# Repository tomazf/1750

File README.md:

# 1750
remote BH1750 light sensor node

HW currently supporting 5 sensors connected over SoftWire library

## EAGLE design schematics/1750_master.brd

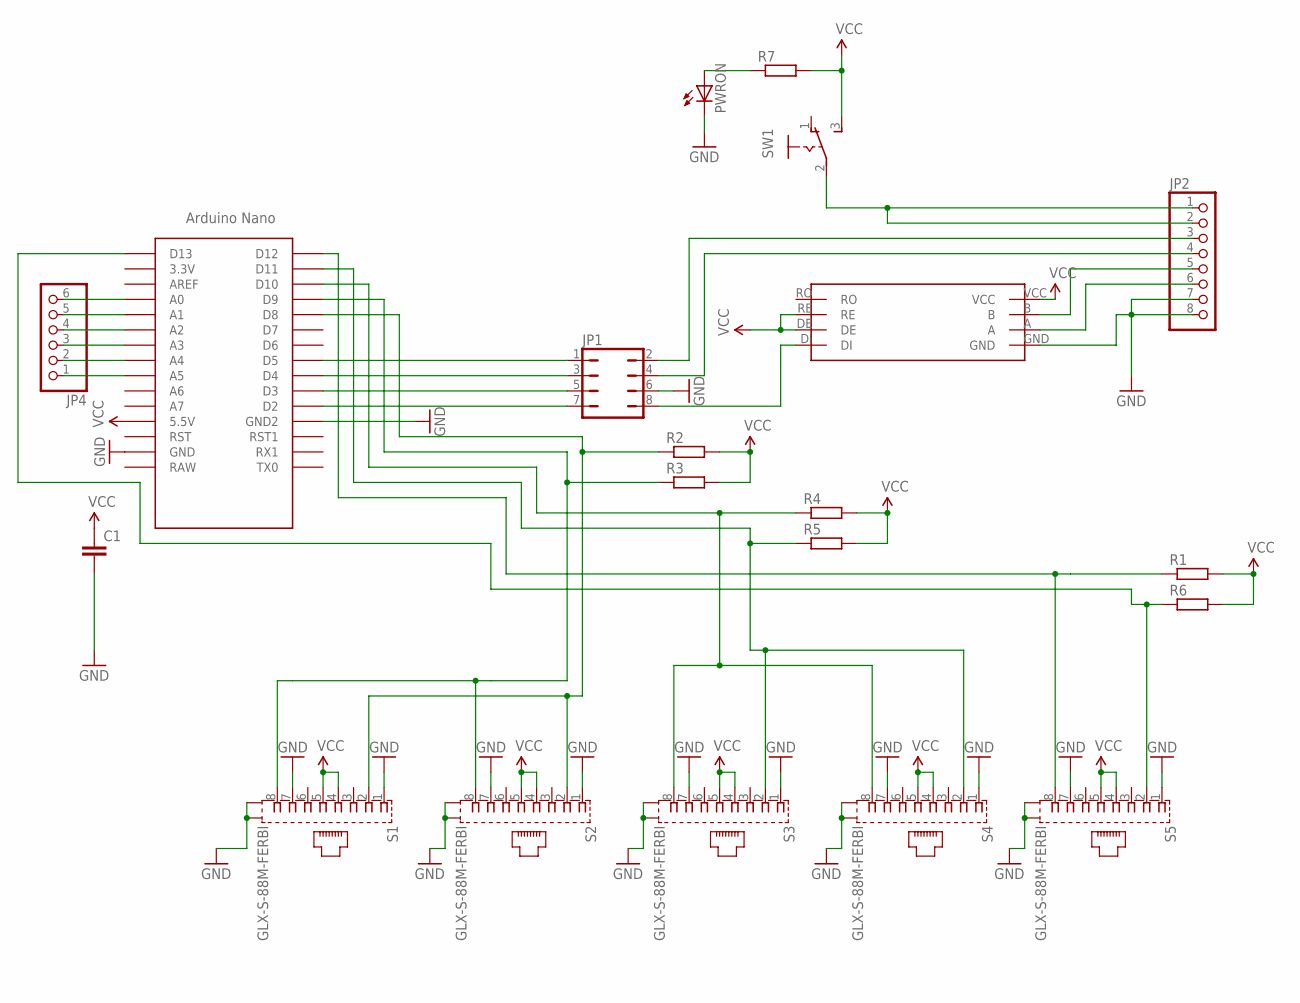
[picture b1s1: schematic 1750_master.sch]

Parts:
C1: C-EU025-025X050; C025-025X050
JP1: JP4Q
JP2: PINHD-1X8; 1X08
JP4: PINHD-1X6; 1X06
PWRON: LED5MM
R1, R2, R3, R4, R5, R6, R7: R-EU_0207/10; 0207/10
S1, S2, S3, S4, S5: GLX-S-88M-FERBI
SW1: 255SB
U$1: NANOF
U$2: 485F

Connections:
GND: C1.2, JP1.6, JP2.7, JP2.8, PWRON.K (C), S1.1, S1.7, S1.S1, S1.S2, S2.1, S2.7, S2.S1, S2.S2, S3.1, S3.7, S3.S1, S3.S2, S4.1, S4.7, S4.S1, S4.S2, S5.1, S5.7, S5.S1, S5.S2, U$1.GND, U$1.GND1 (GND2), U$2.GND
unnamed: JP2.5, U$2.B
unnamed: JP2.6, U$2.A
unnamed: JP1.4, JP2.4
unnamed: JP1.2, JP2.3
unnamed: JP4.1, U$1.A5
unnamed: JP4.2, U$1.A4
unnamed: JP1.5, U$1.D3
unnamed: JP1.7, U$1.D2
unnamed: JP4.3, U$1.A3
unnamed: JP4.4, U$1.A2
unnamed: JP4.5, U$1.A1
unnamed: JP4.6, U$1.A0
unnamed: R4.1, S3.8, S4.8, U$1.D10
unnamed: JP1.8, U$2.DI
unnamed: R5.1, S3.2, S4.2, U$1.D11
unnamed: PWRON.A, R7.1
unnamed: R1.1, S5.8, U$1.D12
unnamed: R6.1, S5.2, U$1.D13
unnamed: JP2.1, JP2.2, SW1.2
unnamed: JP1.3, U$1.D4
unnamed: JP1.1, U$1.D5
SCL: R3.1, S1.8, S2.8, U$1.D9
SDA: R2.1, S1.2, S2.2, U$1.D8
VCC: C1.1, R1.2, R2.2, R3.2, R4.2, R5.2, R6.2, R7.2, S1.4, S1.5, S2.4, S2.5, S3.4, S3.5, S4.4, S4.5, S5.4, S5.5, SW1.3 (S), U$1.5V (5.5V), U$2.DE, U$2.RE, U$2.VCC

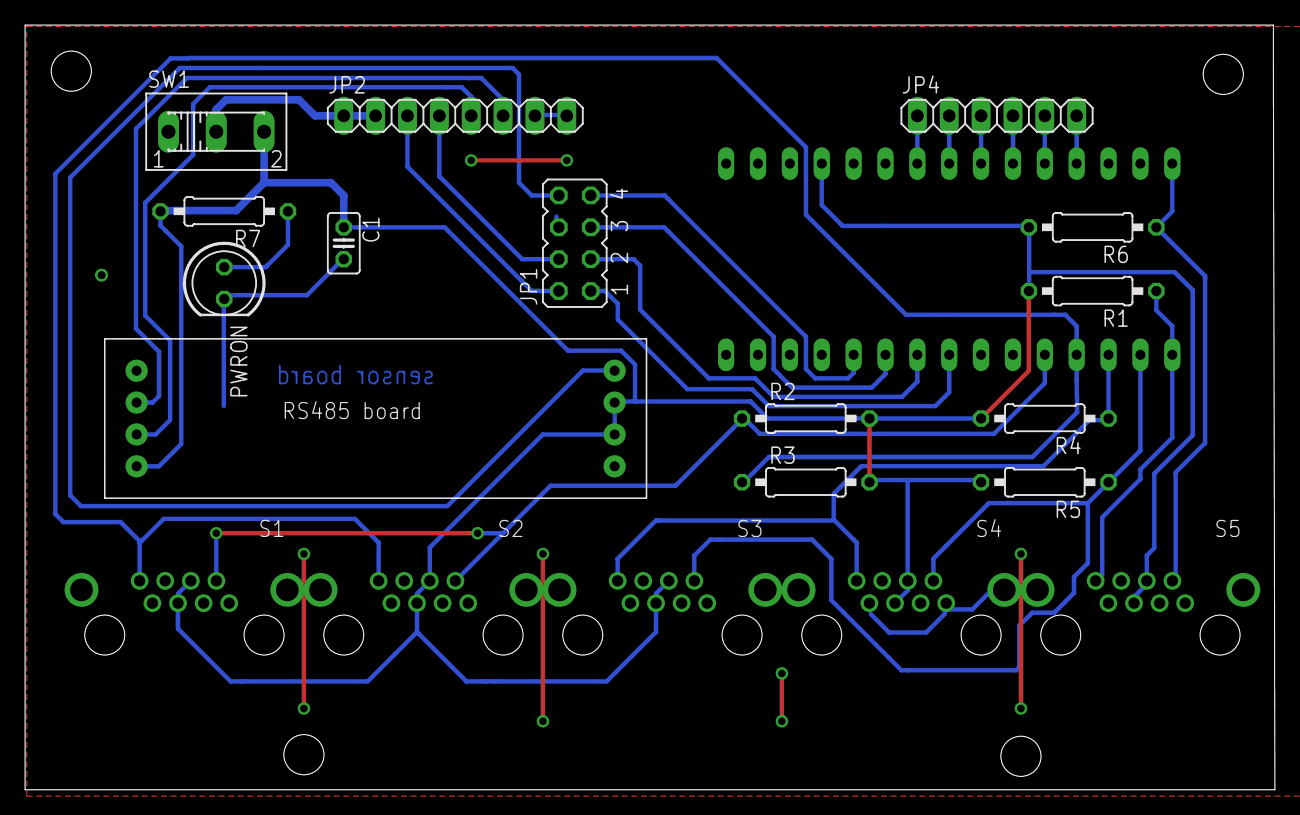
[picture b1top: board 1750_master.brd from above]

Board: 2 copper layers, 99.6 x 61.0 mm, 20 parts (0 on the bottom side), 25 nets.

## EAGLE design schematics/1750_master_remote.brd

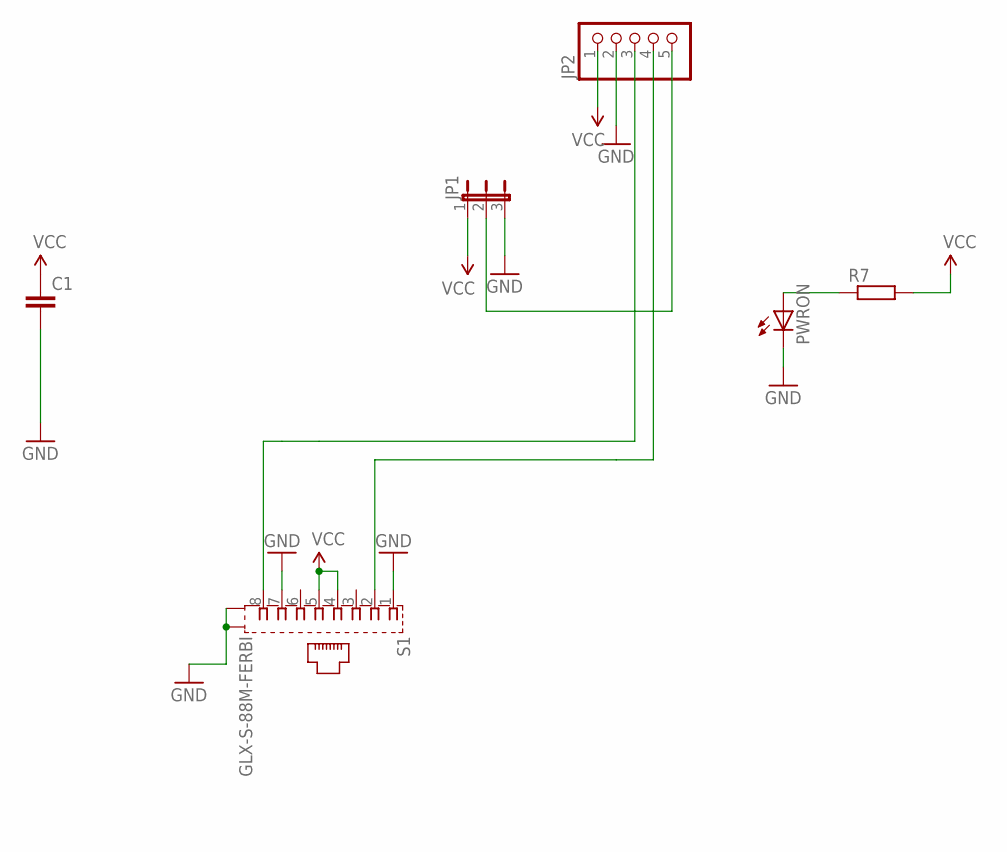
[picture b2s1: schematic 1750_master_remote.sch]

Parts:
C1: C-EU025-025X050; C025-025X050
JP1: JP2E; JP2
JP2: PINHD-1X5; 1X05
PWRON: LED5MM
R7: R-EU_0207/10; 0207/10
S1: GLX-S-88M-FERBI

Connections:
ADDR: JP1.2, JP2.5
GND: C1.2, JP1.3, JP2.2, PWRON.K (C), S1.1, S1.7, S1.S1, S1.S2
unnamed: PWRON.A, R7.1
SCL: JP2.3, S1.8
SDA: JP2.4, S1.2
VCC: C1.1, JP1.1, JP2.1, R7.2, S1.4, S1.5

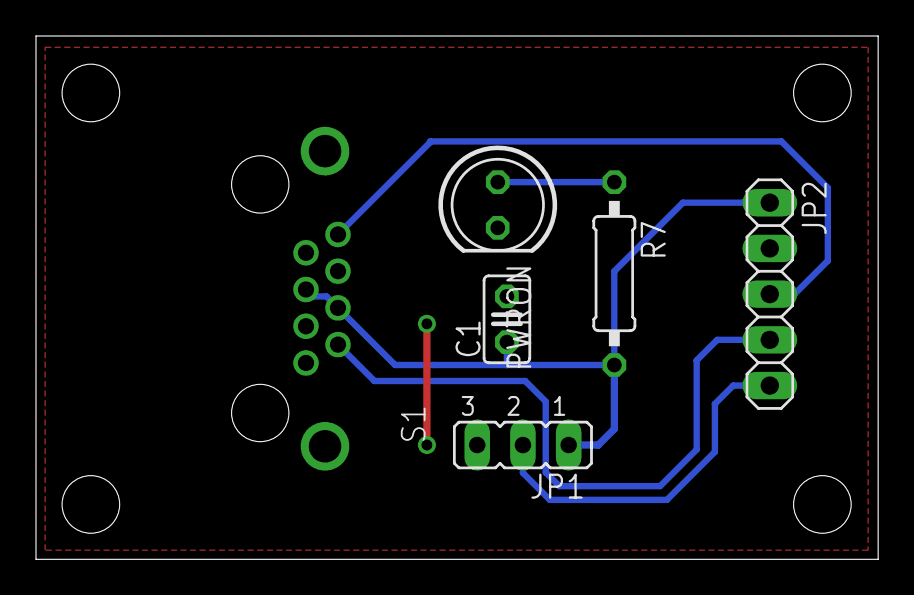
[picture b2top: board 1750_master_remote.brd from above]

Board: 2 copper layers, 46.8 x 29.1 mm, 6 parts (0 on the bottom side), 6 nets.

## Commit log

2018-06-19 Create 1750
2018-06-19 Rename 1750 to 1750.ino

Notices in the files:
parts and their libraries:
SparkFun-Aesthetics: Licensing: Creative Commons ShareAlike 4.0 International - https://creativecommons.org/licenses/by-sa/4.0
